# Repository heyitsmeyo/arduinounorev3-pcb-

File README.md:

# arduinounorev3-pcb-
a custom arduino uno rev3 pcb design

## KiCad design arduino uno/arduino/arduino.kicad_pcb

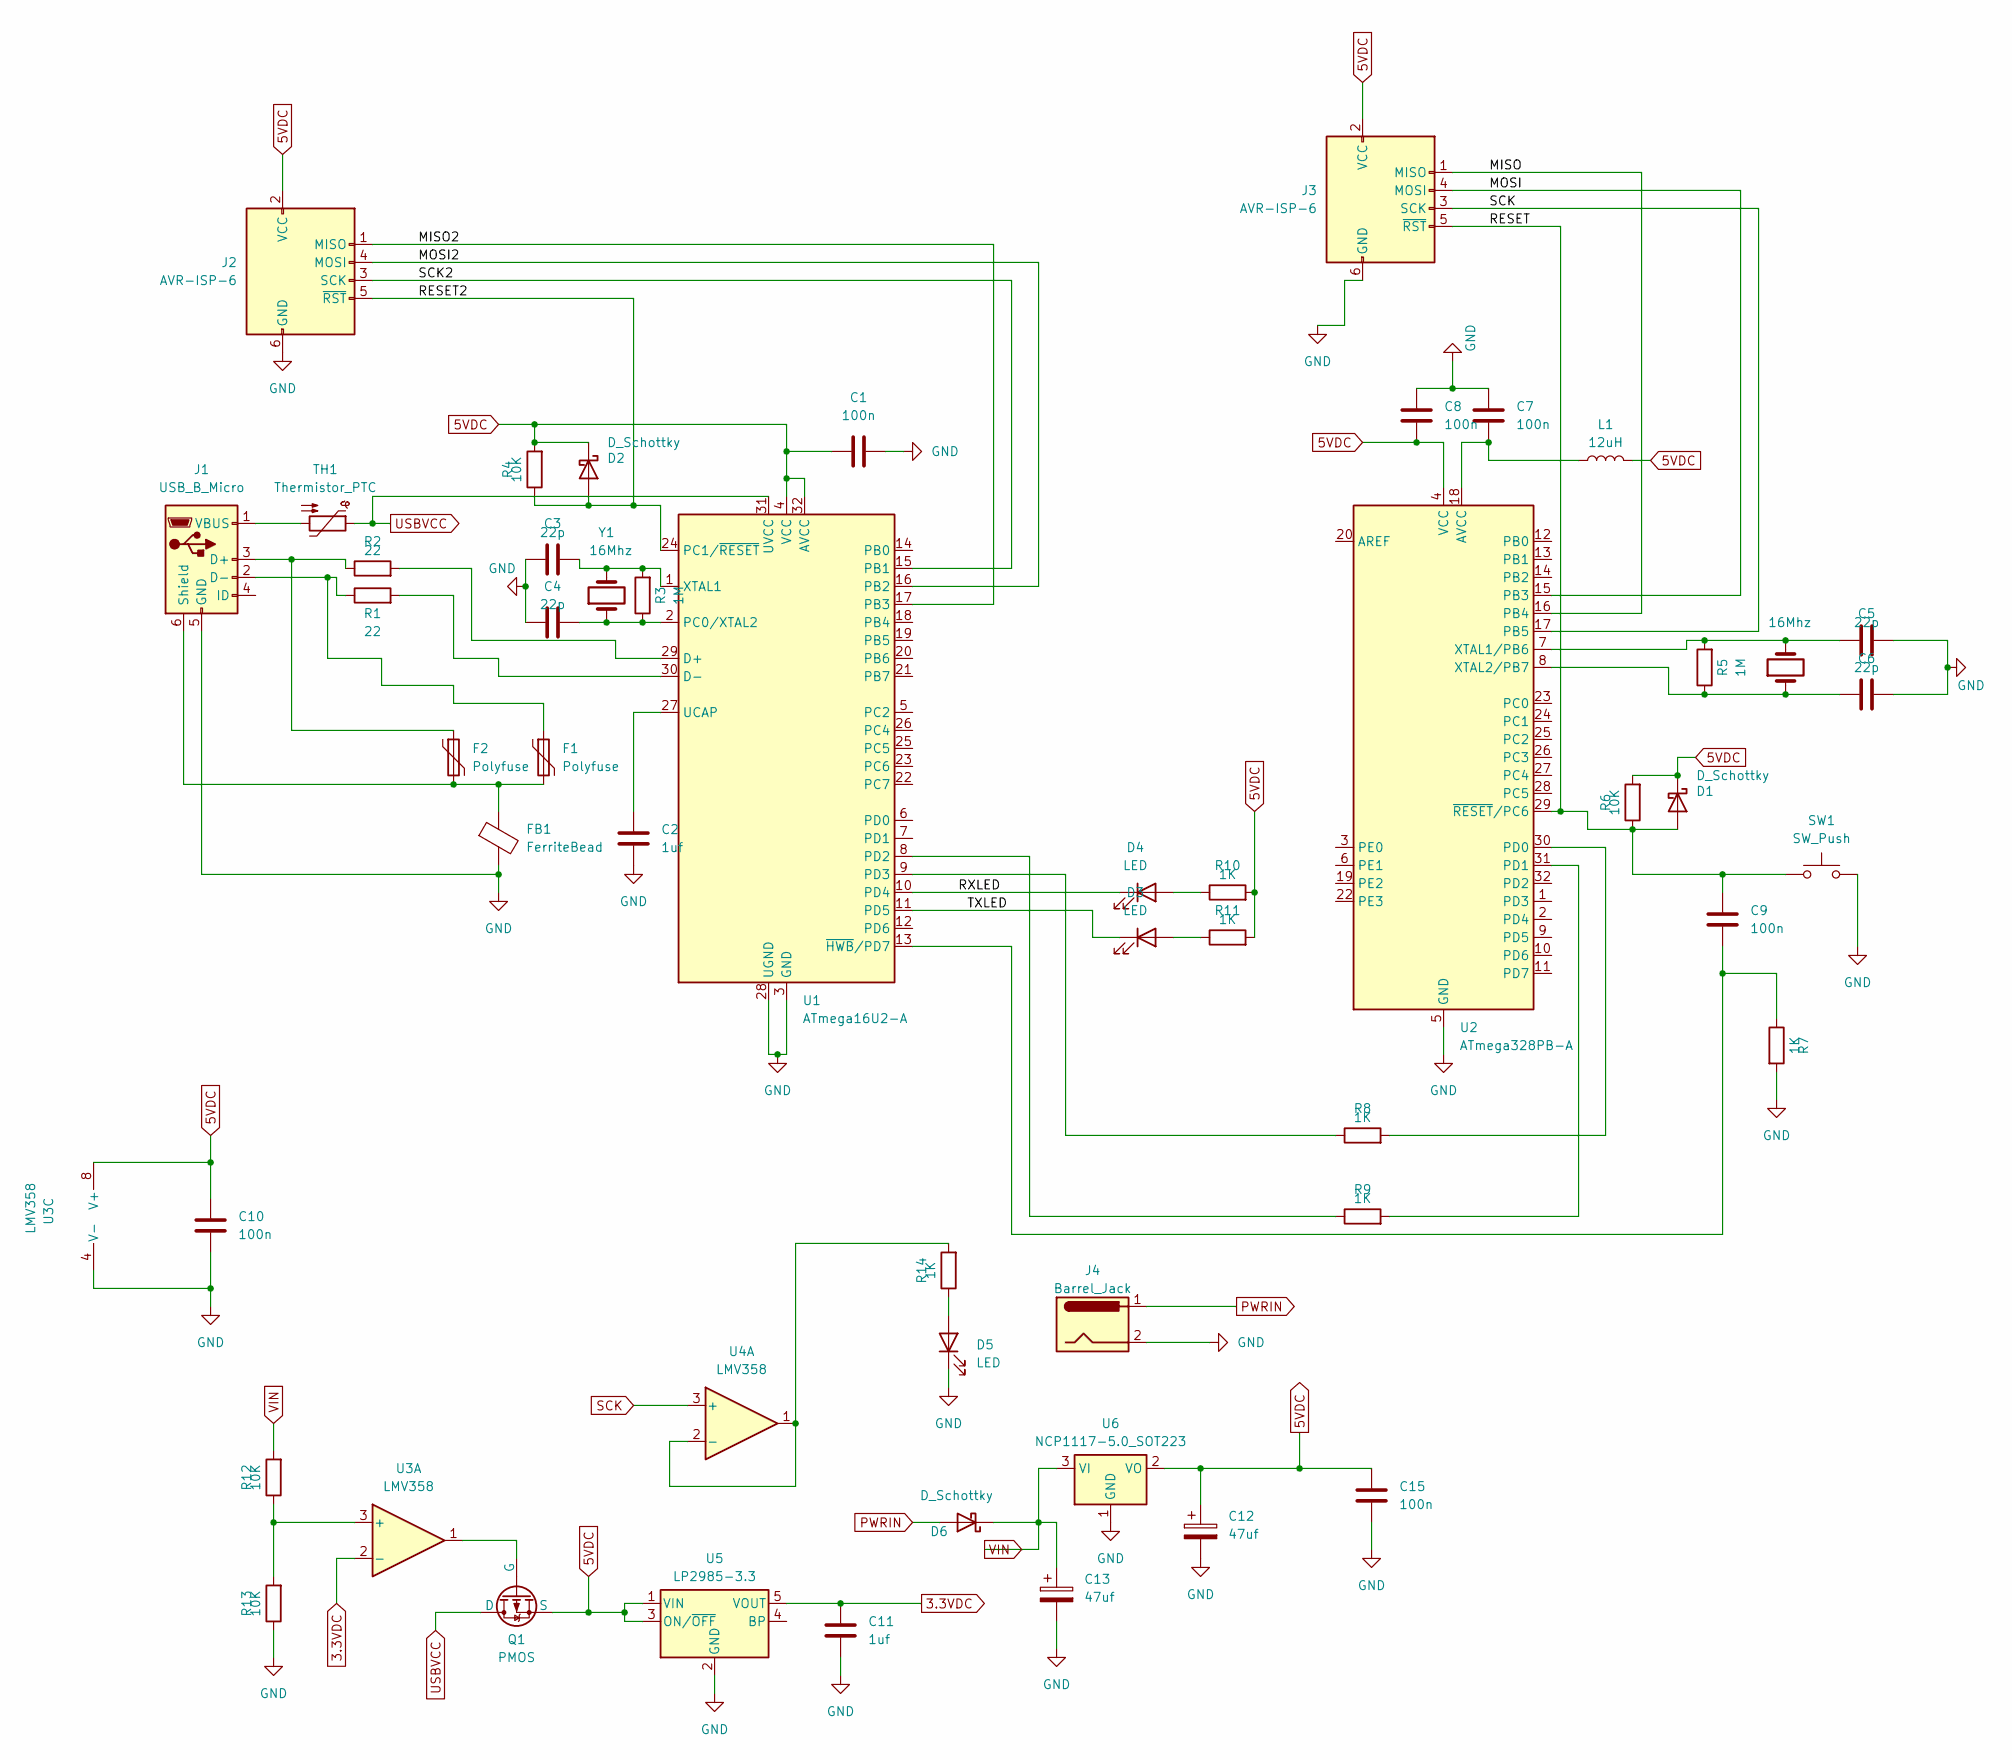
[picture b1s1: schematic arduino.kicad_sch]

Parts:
C1, C7, C8, C9, C10, C15: 100n; C_0603_1608Metric
C2, C11: 1uf; C_0603_1608Metric
C3, C4, C5, C6: 22p; C_0603_1608Metric
C12, C13: 47uf; CP_Elec_6.3x5.8
D1, D2, D6: D_Schottky; D_1206_3216Metric
D3, D4, D5: LED; LED_0603_1608Metric
F1, F2: Polyfuse; R_0603_1608Metric
FB1: FerriteBead; L_0805_2012Metric
J1: USB_B_Micro; USB_Micro-B_Amphenol_10103594-0001LF_Horizontal
J2, J3: AVR-ISP-6; PinHeader_2x03_P2.54mm_Vertical_SMD
J4: Barrel_Jack; BarrelJack_SwitchcraftConxall_RAPC10U_Horizontal
L1: 12uH; L_0201_0603Metric
Q1: PMOS; SOT-23
R1, R2: 22; R_0603_1608Metric
R3, R5: 1M; R_0603_1608Metric
R4, R6, R12, R13: 10K; R_0603_1608Metric
R7, R8, R9, R10, R11, R14: 1K; R_0603_1608Metric
SW1: SW_Push; SW_Tactile_SPST_NO_Straight_CK_PTS636Sx25SMTRLFS
TH1: Thermistor_PTC; R_1812_4532Metric
U1: ATmega16U2-A; TQFP-32_7x7mm_P0.8mm
U2: ATmega328PB-A; TQFP-32_7x7mm_P0.8mm
U3, U4: LMV358; VSSOP-8_3.0x3.0mm_P0.65mm
U5: LP2985-3.3; SOT-23-5
U6: NCP1117-5.0_SOT223; SOT-223-3_TabPin2
Y1, Y2: 16Mhz; Crystal_SMD_Abracon_ABM3-2Pin_5.0x3.2mm

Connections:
3.3VDC: C11.2, U3.2 (-), U5.5 (VOUT)
5VDC: C1.1, C8.1, C10.2, C12.1, C15.2, D1.1 (K), D2.1 (K), J2.2 (VCC), J3.2 (VCC), L1.2, Q1.3 (S), R4.2, R6.2, R10.2, R11.2, U1.4 (VCC), U1.32 (AVCC), U2.4 (VCC), U3.8 (V+), U5.1 (VIN), U5.3 (ON/~OFF), U6.2 (VO)
/MISO: J3.1 (MISO), U2.16 (PB4)
/MISO2: J2.1 (MISO), U1.17 (PB3)
/MOSI: J3.4 (MOSI), U2.15 (PB3)
/MOSI2: J2.4 (MOSI), U1.16 (PB2)
/RESET: C9.2, D1.2 (A), J3.5 (~RST), R6.1, SW1.1, U2.29 (~RESET/PC6)
/RESET2: D2.2 (A), J2.5 (~RST), R4.1, U1.24 (PC1/~RESET)
/RXLED: D4.1 (K), U1.10 (PD4)
/SCK2: J2.3 (SCK), U1.15 (PB1)
GND: C1.2, C2.1, C3.2, C4.1, C5.1, C6.1, C7.1, C8.2, C10.1, C11.1, C12.2, C13.2, C15.1, D5.1 (K), FB1.2, J1.5 (GND), J2.6 (GND), J3.6 (GND), J4.2, R7.2, R13.1, SW1.2, U1.3 (GND), U1.28 (UGND), U2.5 (GND), U2.21 (GND), U3.4 (V-), U5.2 (GND), U6.1 (GND)
unnamed: D3.2 (A), R11.1
unnamed: D3.1 (K), U1.11 (PD5)
unnamed: D4.2 (A), R10.1
unnamed: D5.2 (A), R14.1
unnamed: F2.1, J1.3 (D+), R2.1
unnamed: F1.1, J1.2 (D-), R1.1
unnamed: F1.2, F2.2, FB1.1, J1.6 (Shield)
unnamed: J1.1 (VBUS), TH1.2
unnamed: Q1.2 (G), U3.1
unnamed: R2.2, U1.29 (D+)
unnamed: R1.2, U1.30 (D-)
unnamed: C4.2, R3.1, U1.2 (PC0/XTAL2), Y1.1
unnamed: R9.1, U1.8 (PD2)
unnamed: R8.1, U1.9 (PD3)
unnamed: C2.2, U1.27 (UCAP)
unnamed: C3.1, R3.2, U1.1 (XTAL1), Y1.2
unnamed: C9.1, R7.1, U1.13 (~HWB/PD7)
unnamed: C7.2, L1.1, U2.18 (AVCC)
unnamed: R8.2, U2.30 (PD0)
unnamed: R9.2, U2.31 (PD1)
unnamed: C5.2, R5.2, U2.7 (XTAL1/PB6), Y2.2
unnamed: C6.2, R5.1, U2.8 (XTAL2/PB7), Y2.1
unnamed: R12.1, R13.2, U3.3 (+)
unnamed: R14.2, U3.6 (-), U3.7, U4.1, U4.2 (-)
PWRIN: D6.2 (A), J4.1
SCK: J3.3 (SCK), U2.17 (PB5), U3.5 (+)
USBVCC: Q1.1 (D), TH1.1, U1.31 (UVCC)
VIN: C13.1, D6.1 (K), R12.2, U6.3 (VI)

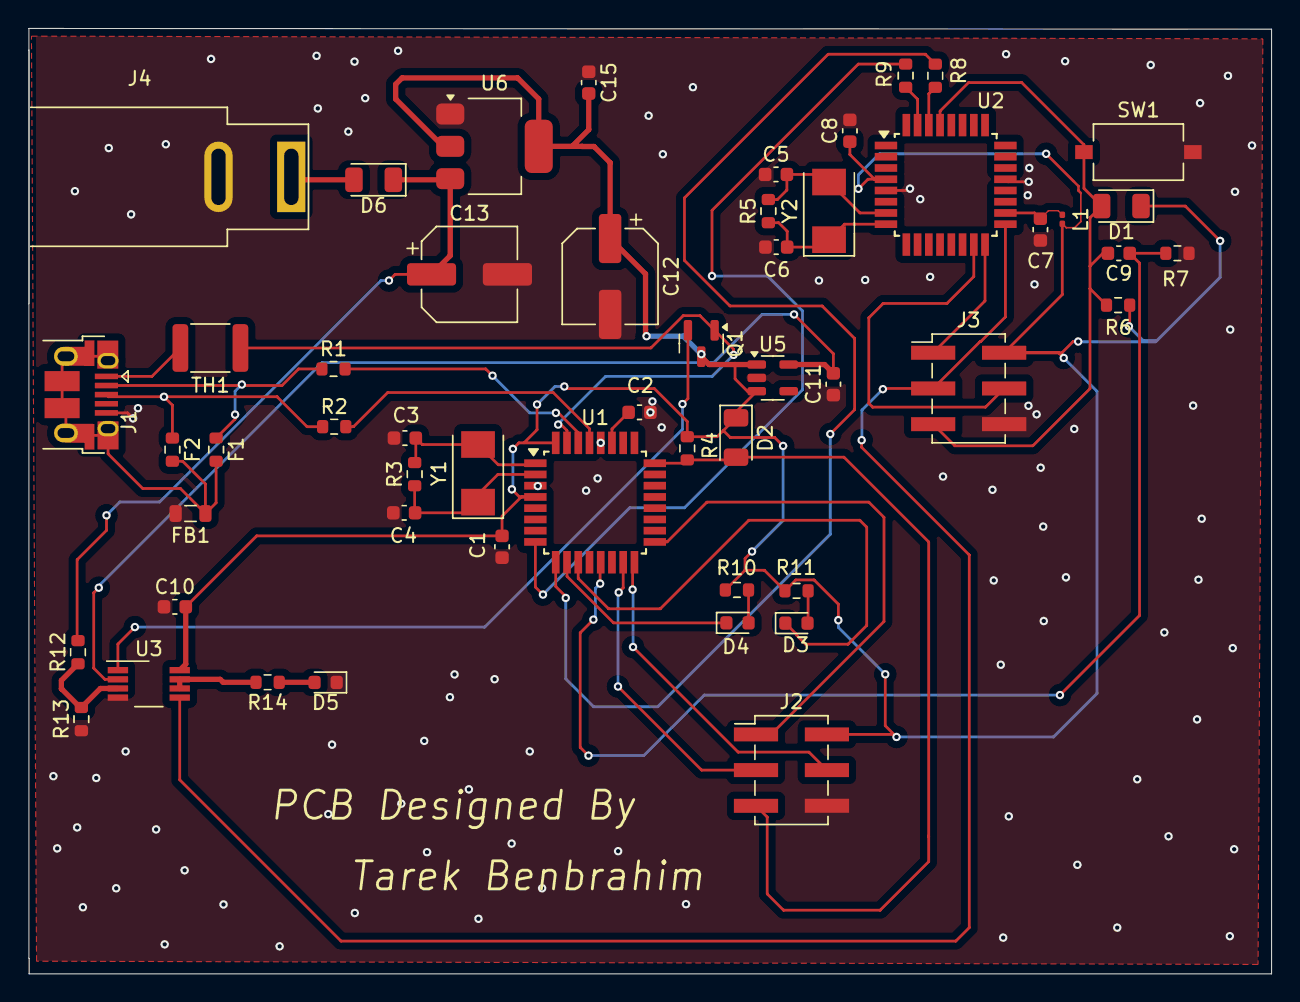
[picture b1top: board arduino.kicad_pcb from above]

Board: 2 copper layers, 88.4 x 67.2 mm, 52 parts (0 on the bottom side), 39 nets.
